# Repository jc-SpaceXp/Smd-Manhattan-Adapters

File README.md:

# SmdManhattanAdapters
PCBs for Manhattan/ugly prototyping

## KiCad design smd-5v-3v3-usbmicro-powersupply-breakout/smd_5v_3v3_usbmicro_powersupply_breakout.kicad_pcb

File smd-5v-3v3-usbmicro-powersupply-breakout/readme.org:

* SMD 5V & 3V3 USB Micro Power Supply Breakout
- A filtered 5V USB VBUS line and 3V3 line via an LDO (all with ESD protection)
** Schematic
[[file:schematic_v04.pdf]]
** BOM
[[file:smd_5v_3v3_usbmicro_powersupply_breakout_bom.csv]]
- MPNs left blank are for generic parts, e.g. the THT header pins (any two pin 2.54mm pitch THT header will suffice)
- FB1 can be interchanged with another appropriately sized ferrite-bead depending on the filtering needs (see below)
*** Alternative FB1 MPNs
- FB1 / 300R @ 100MHz: HI2220R301R-10 (currently using in project)
- FB1 / 100R @ 100MHz: HI2220R101R-10
- FB1 / 550R @ 100MHz: 7427928551
** 3D PCB Models
[[file:pcb_3d_front.png]]
[[file:pcb_3d_back.png]]
** Oscilloscope Analysis
*** VBUS (Unfiltered USB 5V)
- Can see the 5V waveform varies by approx 50-60mV (sloping down from 5V and then periodically jumping back to 5V)
- With the more positive ripple being around 30mV
**** Capture 1
[[file:oscilloscope_captures/vbus/SDS814X_HD_PNG_1.png]]
**** Capture 2
[[file:oscilloscope_captures/vbus/SDS814X_HD_PNG_2_01.png]]
[[file:oscilloscope_captures/vbus/SDS814X_HD_PNG_2_02.png]]
[[file:oscilloscope_captures/vbus/SDS814X_HD_PNG_2_03.png]]
*** 3V3 (LDO) Output
- Very stable output with the ripple being around 20-30mV
- Given the mean of the signal is 3.294V a 30mV ripple is well within spec for the min/max Vout for a 5V signal on the datasheet
**** Capture 1
[[file:oscilloscope_captures/3v3_ldo/SDS814X_HD_PNG_1.png]]
**** Capture 2
[[file:oscilloscope_captures/3v3_ldo/SDS814X_HD_PNG_2_01.png]]
[[file:oscilloscope_captures/3v3_ldo/SDS814X_HD_PNG_2_02.png]]

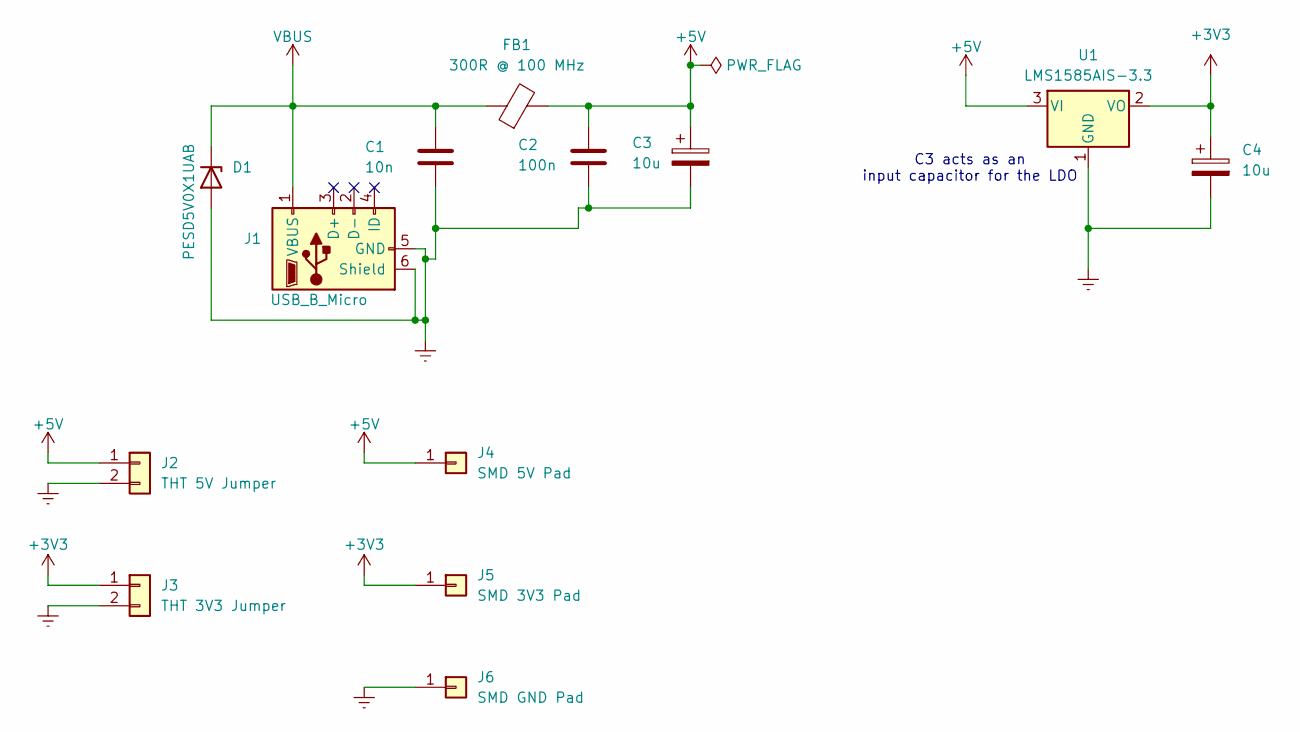
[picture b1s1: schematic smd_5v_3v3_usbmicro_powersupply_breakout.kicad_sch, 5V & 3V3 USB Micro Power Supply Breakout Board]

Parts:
C1: 10n; C_0603_1608Metric
C2: 100n; C_0603_1608Metric
C3, C4: 10u; CP_Elec_4x4.5
D1: PESD5V0X1UAB; D_SOD-523; MPN PESD5V0X1UAB,115
FB1: 300R @ 100 MHz; C_2220_5750Metric_Pad1.97x5.40mm_HandSolder; MPN HI2220R301R-10
J1: USB_B_Micro; USB_Micro-B_Amphenol_10118194-0001LF_Horizontal; MPN 10118194-0001LF
J2: THT 5V Jumper; PinHeader_1x02_P2.54mm_Vertical
J3: THT 3V3 Jumper; PinHeader_1x02_P2.54mm_Vertical
J4: SMD 5V Pad; SolderWirePad_1x01_SMD_5x10mm
J5: SMD 3V3 Pad; SolderWirePad_1x01_SMD_5x10mm
J6: SMD GND Pad; SolderWirePad_1x01_SMD_5x10mm
U1: LMS1585AIS-3.3; TO-263-3_TabPin2; MPN LMS1585AIS-3.3/NOPB

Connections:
+3V3: C4.1, J3.1, J5.1, U1.2 (VO)
+5V: C2.1, C3.1, FB1.2, J2.1, J4.1, U1.3 (VI)
GND: C1.2, C2.2, C3.2, C4.2, D1.2 (A), J1.5 (GND), J1.6 (Shield), J2.2, J3.2, J6.1, U1.1 (GND)
VBUS: C1.1, D1.1 (K), FB1.1, J1.1 (VBUS)

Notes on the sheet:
C3 acts as an input capacitor for the LDO

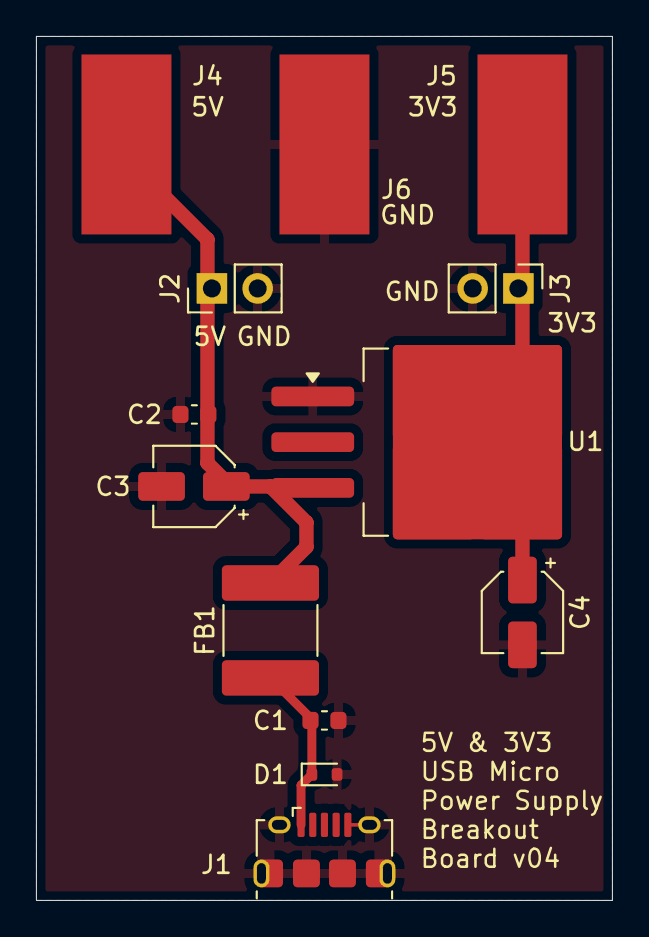
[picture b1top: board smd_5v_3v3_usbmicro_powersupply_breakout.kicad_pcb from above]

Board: 2 copper layers, 32.0 x 48.0 mm, 13 parts (0 on the bottom side), 4 nets.

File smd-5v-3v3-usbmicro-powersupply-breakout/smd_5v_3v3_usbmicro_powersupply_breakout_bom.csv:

"Reference","Value","DNP","MPN","Qty","Footprint","Datasheet"
"C1","10n","","","1","Capacitor_SMD:C_0603_1608Metric","~"
"C2","100n","","","1","Capacitor_SMD:C_0603_1608Metric","~"
"C3,C4","10u","","","2","Capacitor_SMD:CP_Elec_4x4.5","~"
"D1","PESD5V0X1UAB","","PESD5V0X1UAB,115","1","Diode_SMD:D_SOD-523",""
"FB1","300R @ 100 MHz","","HI2220R301R-10","1","Capacitor_SMD:C_2220_5750Metric_Pad1.97x5.40mm_HandSolder","~"
"J1","USB_B_Micro","","10118194-0001LF","1","Connector_USB:USB_Micro-B_Amphenol_10118194-0001LF_Horizontal","~"
"J2","THT 5V Jumper","","","1","Connector_PinHeader_2.54mm:PinHeader_1x02_P2.54mm_Vertical","~"
"J3","THT 3V3 Jumper","","","1","Connector_PinHeader_2.54mm:PinHeader_1x02_P2.54mm_Vertical","~"
"U1","LMS1585AIS-3.3","","LMS1585AIS-3.3/NOPB","1","Package_TO_SOT_SMD:TO-263-3_TabPin2","http://www.ti.com/lit/ds/symlink/lm1084.pdf"

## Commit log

2024-11-18 Add footprints from dip 30 w15.24 ics
    - Needed for STM Nucleo KB boards (and Arduino Nanos too)
2024-11-18 Add kicad project files
    - Note: schematic is blank
2024-11-18 Add pdf/jpg of pcb
    - For those without KiCad
2024-11-18 Add .gitignore
    - Ignore KiCad backup files
2024-11-18 Update .gitignore
    - Ignore KiCad footprint cache files
2024-11-18 Update pcb info (text fields)
2025-02-10 Iniital commit for 5v & 3v3 usb micro psu
    - Schematic taken from my Spekky Matrix schematic
    - Idea is for a simple 5V & 3V3 PSU from a 5V VBUS input via USB micro
    connector
2025-02-10 Update tvs diode
    - Actually picked a part rather than a placeholder one
2025-02-11 Update ferrite bead (schematic)
    - 2220 imperial SMD package size seems to have a decent amount of
    components currently available for a wide range of impedances
    - TI SPRAAR7A doc suggests a ferribe bead between 47 and 1000 ohms rated
    at 100MHz with the ferrite bead continuing to be resistive at 1GHz
    - Seen various different rated ferrite beads on VBUS line which supports
    the above claim
2025-02-11 Add part number for usb b micro connector
2025-02-11 Exclude smd pads from bom
    - They are just exposed copper, no need for them to be on the BOM
2025-02-11 Initial pcb commit
    - Rough placement of components to a 1mm grid
2025-02-11 Hide smd pad 3d model
    - Only wires will be connected here
2025-02-11 Better placement of components on pcb
2025-02-11 Narrow pcb edge cuts
2025-02-11 Add ground pours
2025-02-11 Import OSHPark DRC settings
2025-02-11 Import track sizes from another project
2025-02-11 All pcb traces/connections set
2025-02-11 Update schematic and pcb
    - Having the 3 pin connectors was awkward, split them up into two
    separate connectors for each power plane
2025-02-11 Clean up silkscreen
2025-02-11 Connect missing ground connection on usb connector
2025-02-11 Ignore ldo pin 2 unconnected (drc)
    - Pin 2 is connected from the exposed tab (not from the 3 pin section)
    - Excluded DRC violation to stop producing errors
    - Alternatively can change the footprint to exclude the 2nd pin but map
    the tab to pin 2
2025-02-11 Update pcb default silkscreen thickness (oshpark)
    - Matches oshpark setting and DRC settings
2025-02-11 Clearer silkscreen for components
    - Added 5V/3V3/GND silkscreen for SMD and THT connectors
2025-02-11 Update revision numbers
    - Should of updated after updating the PCB and schematic
2025-02-11 Add project info silkscreen to pcb
2025-02-11 Add 3d render photos to repo
2025-02-11 v03 update (remove LDO input capacitor)
    - LDO input capacitor isn't required as the pi-filter should reduce the
    ripples on the VBUS line giving us a "cleaner" 5V line therefore
    another input capacitor on the LDO isn't required (as there shouldn't
    be excessive rippling/noise)
2025-02-11 Update readme (main project)
2025-02-11 Add schmeatic pdf to project
2025-02-11 Add readme for power supply breakout
2025-02-11 Correct directory name
2025-02-11 Update readmes
2025-02-11 Add readme for dip30 w15.24mm adapter
2025-02-11 Update 3d renders for dip30 w15.24mm adapter
2025-02-11 Remove old pcb 3d render (jpg)
2025-02-11 Hide dip30 w15.24mm 3d model
2025-02-11 Update usb micro psu (v04)
    - Added a GND SMD pad
    - Updated readme, schematic and 3d renders
2025-03-12 Kicad v9 schematic update (smd 5v/3v3 psu)
2025-03-12 Update tvs diode part number
    - Mouser incorrectly listed a bidrectional diode as a unidirectional one
    - Corrected the part number to a unidirectional TVS diode with similar
    specs
2025-03-12 Kicad v9 pcb update (smd 5v/3v3 psu)
    - Also corrected TVS diode part name
2025-03-12 Correct spacing in part numbers (smd 5v/3v3 psu)
2025-03-12 Setup export of bom (smd 5v/3v3 psu)
2025-03-12 Add bom for smd 5v/3v3 psu
2025-03-12 Update readme (smd 5v/3v3 psu)
2025-03-12 Add oscilloscope data capture for smd 5v/3v3 psu
    - Updated readme too
2025-03-12 Add 3v3 ldo vout signal captures (smd 5v/3v3 psu)
    - Updated readme too
2025-03-12 Update readme (formatting, smd 5v/3v3 psu)
